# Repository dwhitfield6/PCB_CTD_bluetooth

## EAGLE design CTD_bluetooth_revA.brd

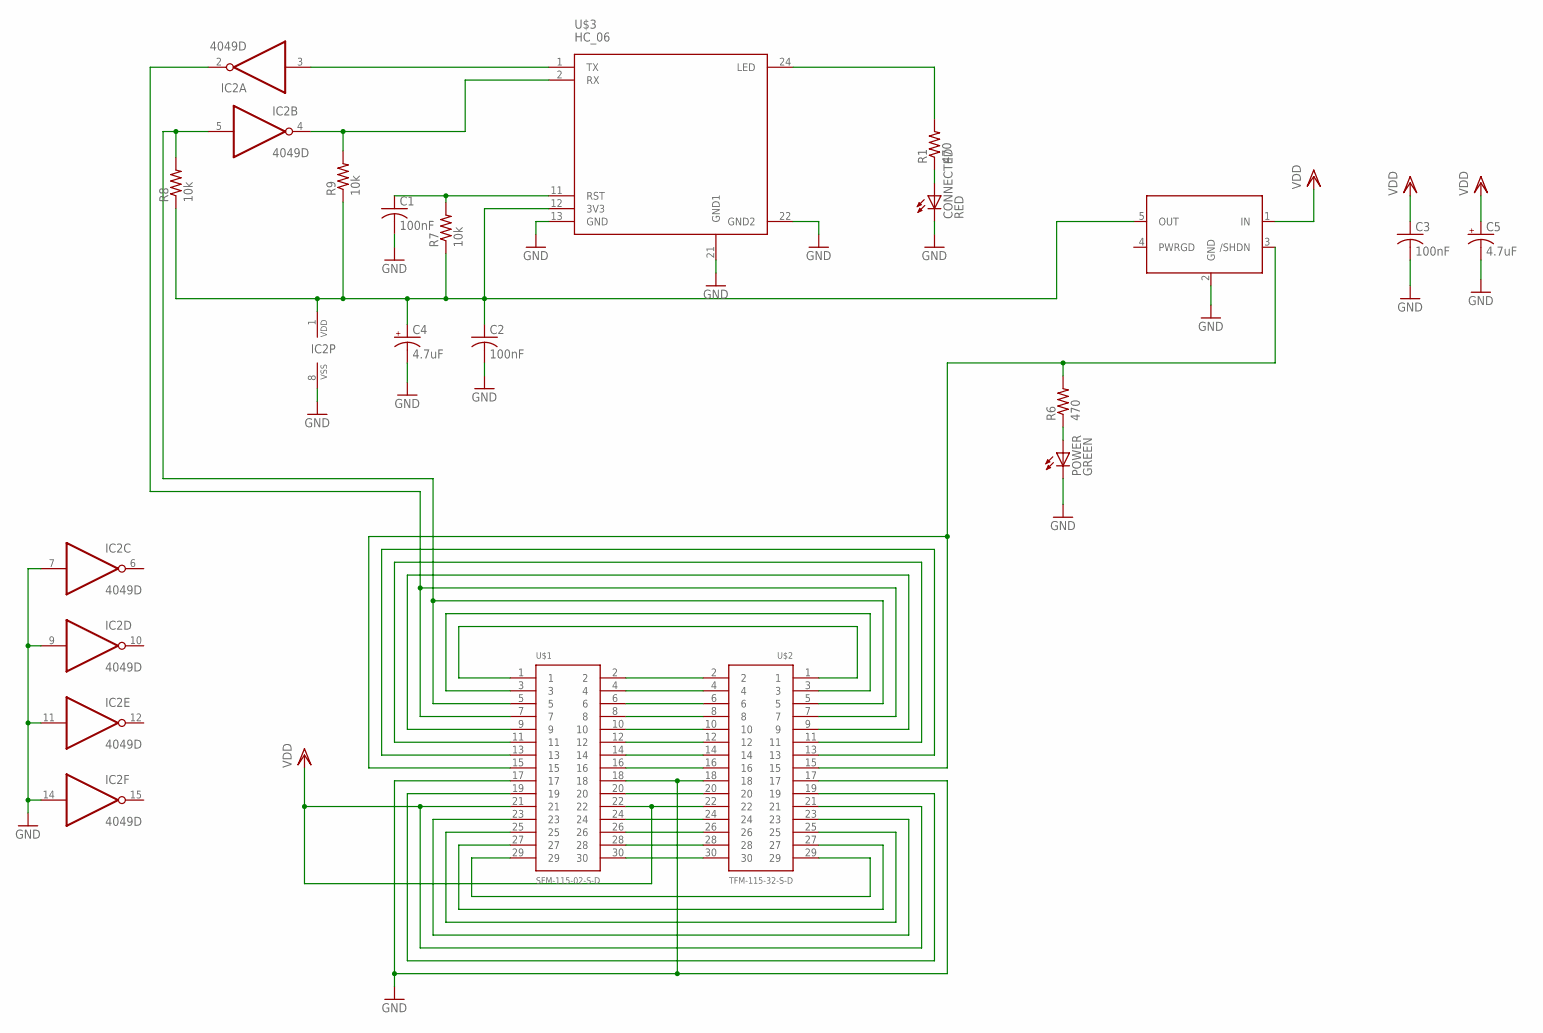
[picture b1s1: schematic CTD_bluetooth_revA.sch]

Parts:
C1, C2, C3: 100nF; C050-024X044
C4, C5: 4.7uF; 153CLV-0505
CONNECTED: RED; 1206
IC2: 4049D; SO16
POWER: GREEN; 1206
R1, R6: 470; R5025
R7, R8, R9: 10k; R5025
U$1: SFM-115-02-S-D
U$2: TFM-115-32-S-D
U$3: HC_06; BLUETOOTH_SMD_HC06
U$4: MCP1755T; SOT23-5

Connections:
3V3: C2.1, C4.+, IC2.1 (VDD), R7.1, R8.1, R9.1, U$3.12 (3V3), U$4.5 (OUT)
GND: C1.2, C2.2, C3.2, C4.-, C5.-, CONNECTED.C, IC2.7 (I), IC2.8 (VSS), IC2.9 (I), IC2.11 (I), IC2.14 (I), POWER.C, U$1.17, U$1.18, U$2.17, U$2.18, U$3.13 (GND), U$3.21 (GND1), U$3.22 (GND2), U$4.2 (GND)
unnamed: U$1.2, U$2.2
unnamed: U$1.4, U$2.4
unnamed: CONNECTED.A, R1.1
unnamed: U$1.6, U$2.6
unnamed: U$1.10, U$2.10
unnamed: U$1.12, U$2.12
unnamed: U$1.14, U$2.14
unnamed: U$1.8, U$2.8
unnamed: U$1.16, U$2.16
unnamed: U$1.20, U$2.20
unnamed: POWER.A, R6.1
unnamed: U$1.24, U$2.24
unnamed: U$1.26, U$2.26
unnamed: U$1.28, U$2.28
unnamed: U$1.30, U$2.30
unnamed: U$1.1, U$2.1
unnamed: U$1.3, U$2.3
unnamed: U$1.9, U$2.9
unnamed: U$1.11, U$2.11
unnamed: U$1.13, U$2.13
unnamed: U$1.29, U$2.29
unnamed: U$1.27, U$2.27
unnamed: U$1.25, U$2.25
unnamed: U$1.23, U$2.23
unnamed: U$1.19, U$2.19
unnamed: R1.2, U$3.24 (LED)
unnamed: C1.1, R7.2, U$3.11 (RST)
RX: IC2.5 (I), R8.2, U$1.5, U$2.5
RXPRE: IC2.4 (O), R9.2, U$3.2 (RX)
SHUTDOWN: R6.2, U$1.15, U$2.15, U$4.3 (/SHDN)
TX: IC2.2 (O), U$1.7, U$2.7
TXPRE: IC2.3 (I), U$3.1 (TX)
VDD: C3.1, C5.+, U$1.21, U$1.22, U$2.21, U$2.22, U$4.1 (IN)

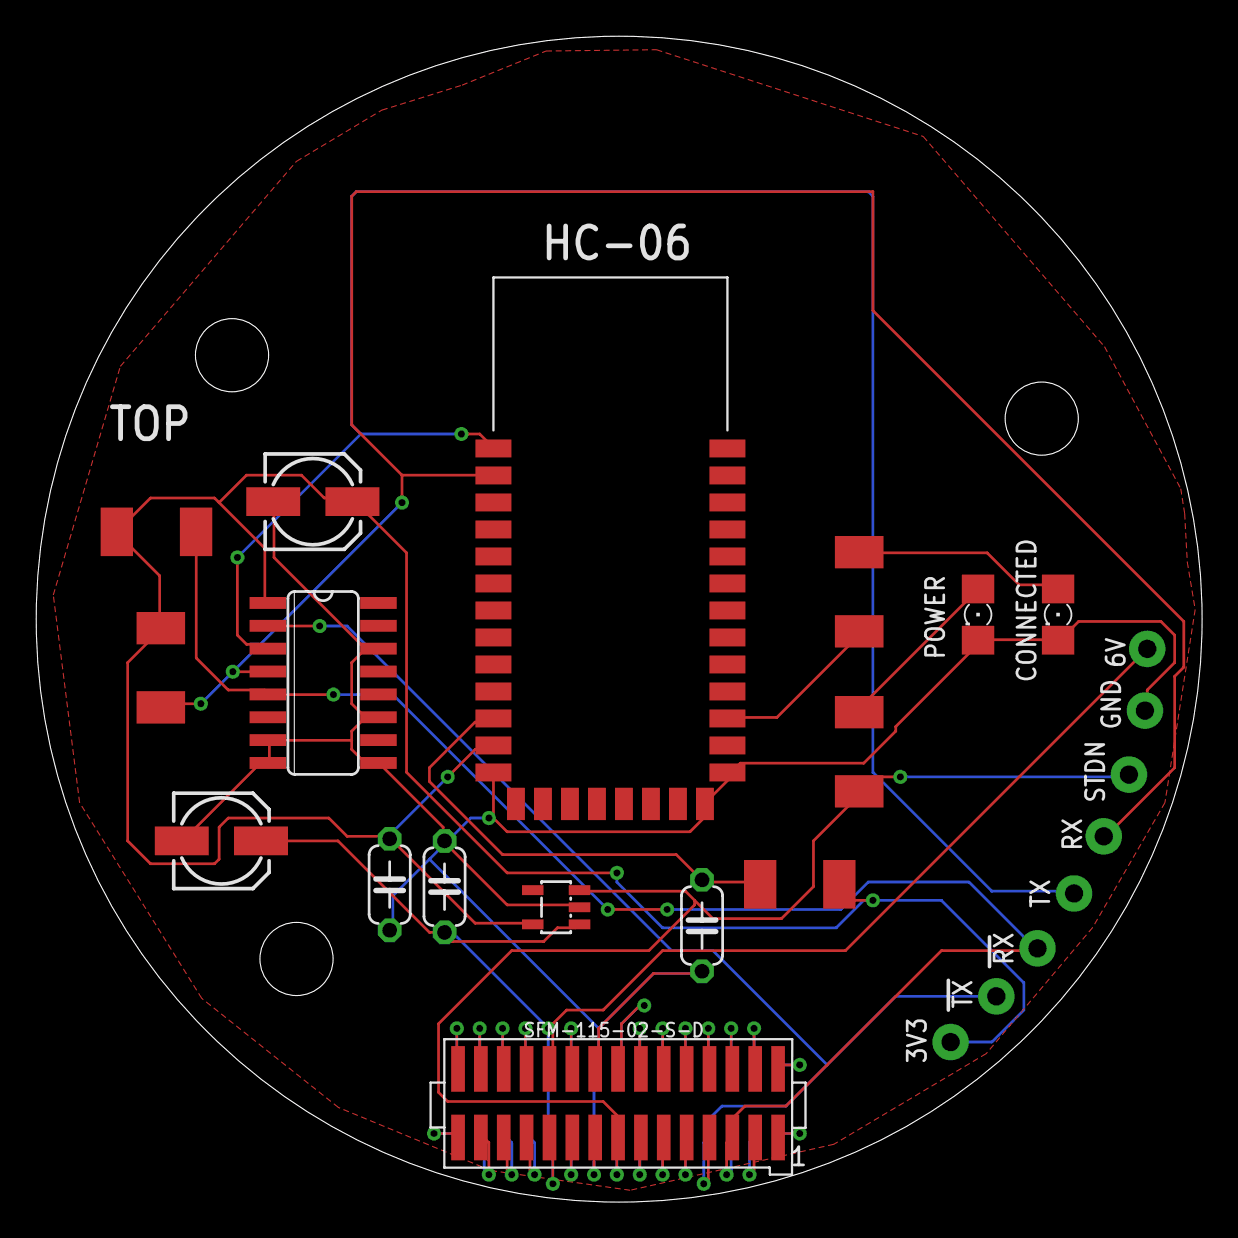
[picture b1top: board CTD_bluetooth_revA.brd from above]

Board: 2 copper layers, 64.8 x 64.8 mm, 17 parts (1 on the bottom side), 35 nets.

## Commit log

2015-01-31 :confetti_ball: Added .gitattributes & .gitignore files
2015-01-31 Create
    - Created
